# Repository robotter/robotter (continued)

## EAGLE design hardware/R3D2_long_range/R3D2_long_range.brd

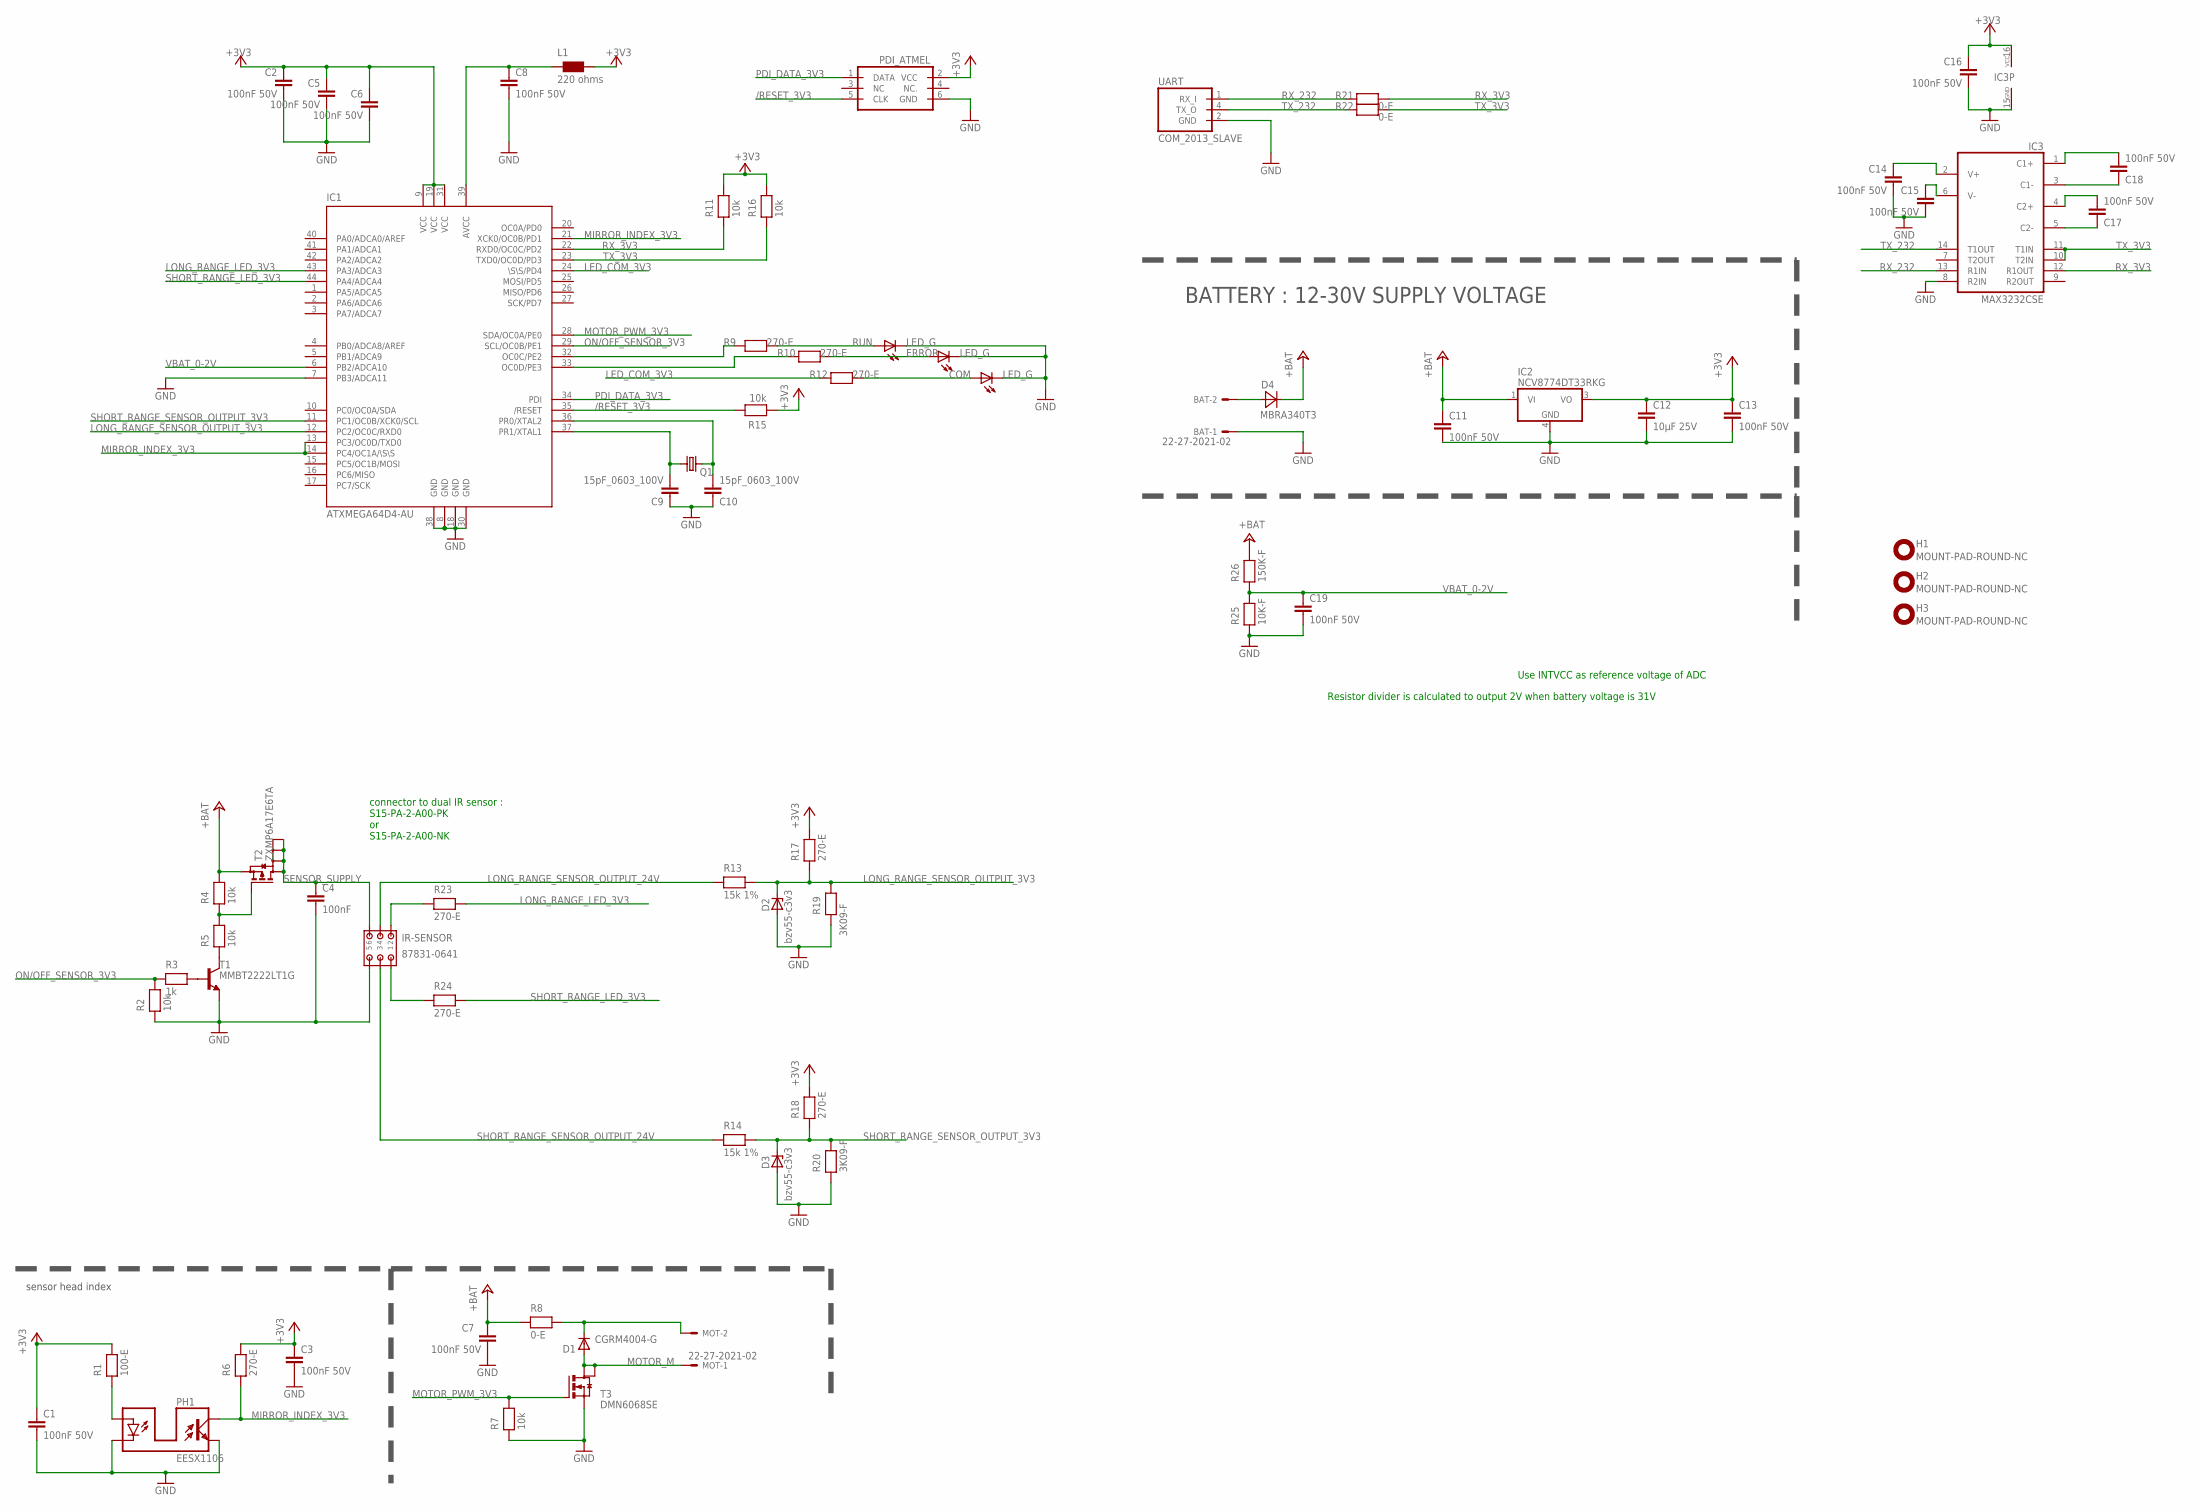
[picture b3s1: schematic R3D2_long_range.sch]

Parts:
BAT: 22-27-2021-02; 6410-02
C1, C2, C3, C5, C6, C7, C8, C13, C14, C15, C16, C17, C18: 100nF 50V; C0603
C4: 100nF; C0603
C9, C10: 15pF_0603_100V; C0603
C11, C19: 100nF 50V; C0805
C12: 10µF 25V; C1210
COM: LED_G; CHIP-LED0805
D1: CGRM4004-G; SOD-123_MINI-SMA
D2, D3: bzv55-c3v3; SOD80C
D4: MBRA340T3; SMA
ERROR: LED_G; CHIP-LED0805
H1, H2, H3: MOUNT-PAD-ROUND-NC; 3,0-PAD_NC
IC1: ATXMEGA64D4-AU; TQFP44
IC2: NCV8774DT33RKG; DPACK_3
IC3: MAX3232CSE; SO16
IR-SENSOR: 87831-0641
L1: 220 ohms; R0603
MOT: 22-27-2021-02; 6410-02
PDI_ATMEL: PDI_ATMELL; ML6L
PH1: EESX1106
Q1: CRYSTAL_16MHZ_5032; CRYSTAL_5032
R1: 100-E; R0805
R2, R4, R5, R7, R11, R15, R16: 10k; R0603
R3: 1k; R0603
R6, R9, R10, R12, R17, R18, R23, R24: 270-E; R0805
R8, R21, R22: 0-E; R0805
R13, R14: 15k 1%; R0603
R19, R20: 3K09-F; R0603
R25: 10K-F; R0603
R26: 150K-F; R0603
RUN: LED_G; CHIP-LED0805
T1: MMBT2222LT1G; SOT23-BEC
T2: ZXMP6A17E6TA; SOT26
T3: DMN6068SE; SOT223
UART: COM_2013_SLAVE; MICROMATCH-4_SMD

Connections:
+3V3: C1.1, C2.1, C3.1, C5.1, C6.1, C12.1, C13.1, C16.1, IC1.9 (VCC), IC1.19 (VCC), IC1.31 (VCC), IC2.3 (VO), IC3.16 (VCC), L1.2, PDI_ATMEL.2 (VCC), R1.2, R6.2, R11.2, R15.1, R16.2, R17.2, R18.2
+24V: C7.1, C11.1, D4.C, IC2.1 (VI), R4.2, R8.1, R26.2, T2.4 (S)
/RESET_3V3: IC1.35 (/RESET), PDI_ATMEL.5 (CLK), R15.2
GND: BAT.1, C1.2, C2.2, C3.2, C4.2, C5.2, C6.2, C7.2, C8.2, C9.1, C10.1, C11.2, C12.2, C13.2, C14.2, C15.2, C16.2, C19.2, COM.C, D2.A, D3.A, ERROR.C, IC1.7 (PB3/ADCA11), IC1.8 (GND), IC1.18 (GND), IC1.30 (GND), IC1.38 (GND), IC2.4 (GND), IC3.8 (R2IN), IC3.15 (GND), IR-SENSOR.5, PDI_ATMEL.6 (GND), PH1.E (TRANSISTOR_E), PH1.K (LED_C), R2.1, R7.1, R19.1, R20.1, R25.1, RUN.C, T1.E, T3.3 (S), UART.2 (GND)
LED_COM_3V3: IC1.24 (\S\S/PD4), R12.1
LONG_RANGE_LED_3V3: IC1.43 (PA3/ADCA3), R23.2
LONG_RANGE_SENSOR_OUTPUT_3V3: D2.C, IC1.12 (PC2/OC0C/RXD0), R13.2, R17.1, R19.2
LONG_RANGE_SENSOR_OUTPUT_24V: IR-SENSOR.4, R13.1
MIRROR_INDEX_3V3: IC1.13 (PC3/OC0D/TXD0), IC1.14 (PC4/OC1A/\S\S), IC1.21 (XCK0/OC0B/PD1), PH1.C (TRANSISTOR_C), R6.1
MOTOR_M: D1.A, MOT.1, T3.2 (D), T3.4 (D)
MOTOR_PWM_3V3: IC1.28 (SDA/OC0A/PE0), R7.2, T3.1 (G)
unnamed: C18.1, IC3.1 (C1+)
unnamed: R9.2, RUN.A
unnamed: D1.C, MOT.2, R8.2
unnamed: ERROR.A, R10.2
unnamed: C18.2, IC3.3 (C1-)
unnamed: C17.1, IC3.4 (C2+)
unnamed: COM.A, R12.2
unnamed: BAT.2, D4.A
unnamed: IC1.32 (OC0C/PE2), R9.1
unnamed: IC1.33 (OC0D/PE3), R10.1
unnamed: C14.1, IC3.2 (V+)
unnamed: C15.1, IC3.6 (V-)
unnamed: C10.2, IC1.36 (PR0/XTAL2), Q1.2
unnamed: PH1.A (LED_A), R1.1
unnamed: C8.1, IC1.39 (AVCC), L1.1
unnamed: IR-SENSOR.2, R23.1
unnamed: IR-SENSOR.1, R24.1
unnamed: C17.2, IC3.5 (C2-)
unnamed: C9.2, IC1.37 (PR1/XTAL1), Q1.1
unnamed: R3.2, T1.B
unnamed: R5.1, T1.C
unnamed: R4.1, R5.2, T2.3 (G)
ON/OFF_SENSOR_3V3: IC1.29 (SCL/OC0B/PE1), R2.2, R3.1
PDI_DATA_3V3: IC1.34 (PDI), PDI_ATMEL.1 (DATA)
RX_3V3: IC1.22 (RXD0/OC0C/PD2), IC3.12 (R1OUT), R11.1, R21.2
RX_232: IC3.13 (R1IN), R21.1, UART.1 (RX_I)
SENSOR_SUPPLY: C4.1, IR-SENSOR.6, T2.1 (D), T2.2 (D), T2.5 (D), T2.6 (D)
SHORT_RANGE_LED_3V3: IC1.44 (PA4/ADCA4), R24.2
SHORT_RANGE_SENSOR_OUTPUT_3V3: D3.C, IC1.11 (PC1/OC0B/XCK0/SCL), R14.2, R18.1, R20.2
SHORT_RANGE_SENSOR_OUTPUT_24V: IR-SENSOR.3, R14.1
TX_3V3: IC1.23 (TXD0/OC0D/PD3), IC3.10 (T2IN), IC3.11 (T1IN), R16.1, R22.2
TX_232: IC3.14 (T1OUT), R22.1, UART.4 (TX_O)
VBAT_0-2V: C19.1, IC1.6 (PB2/ADCA10), R25.2, R26.1

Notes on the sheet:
sensor head index
connector to dual IR sensor : S15-PA-2-A00-PK or S15-PA-2-A00-NK
BATTERY : 12-30V SUPPLY VOLTAGE
Use INTVCC as reference voltage of ADC
Resistor divider is calculated to output 2V when battery voltage is 31V

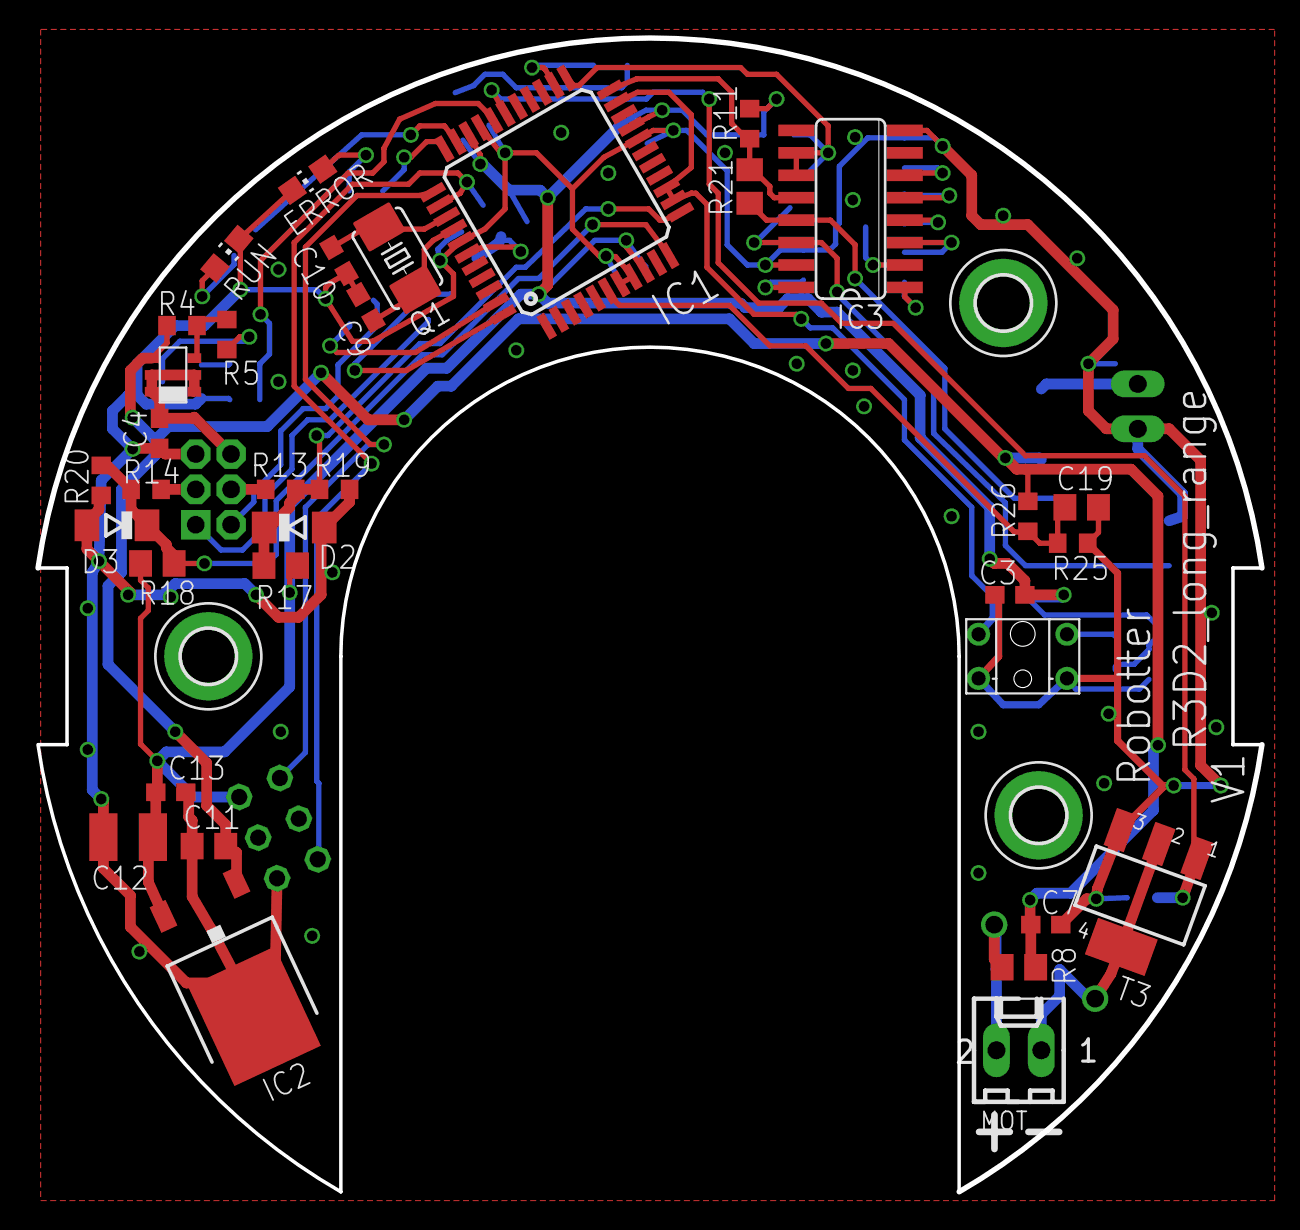
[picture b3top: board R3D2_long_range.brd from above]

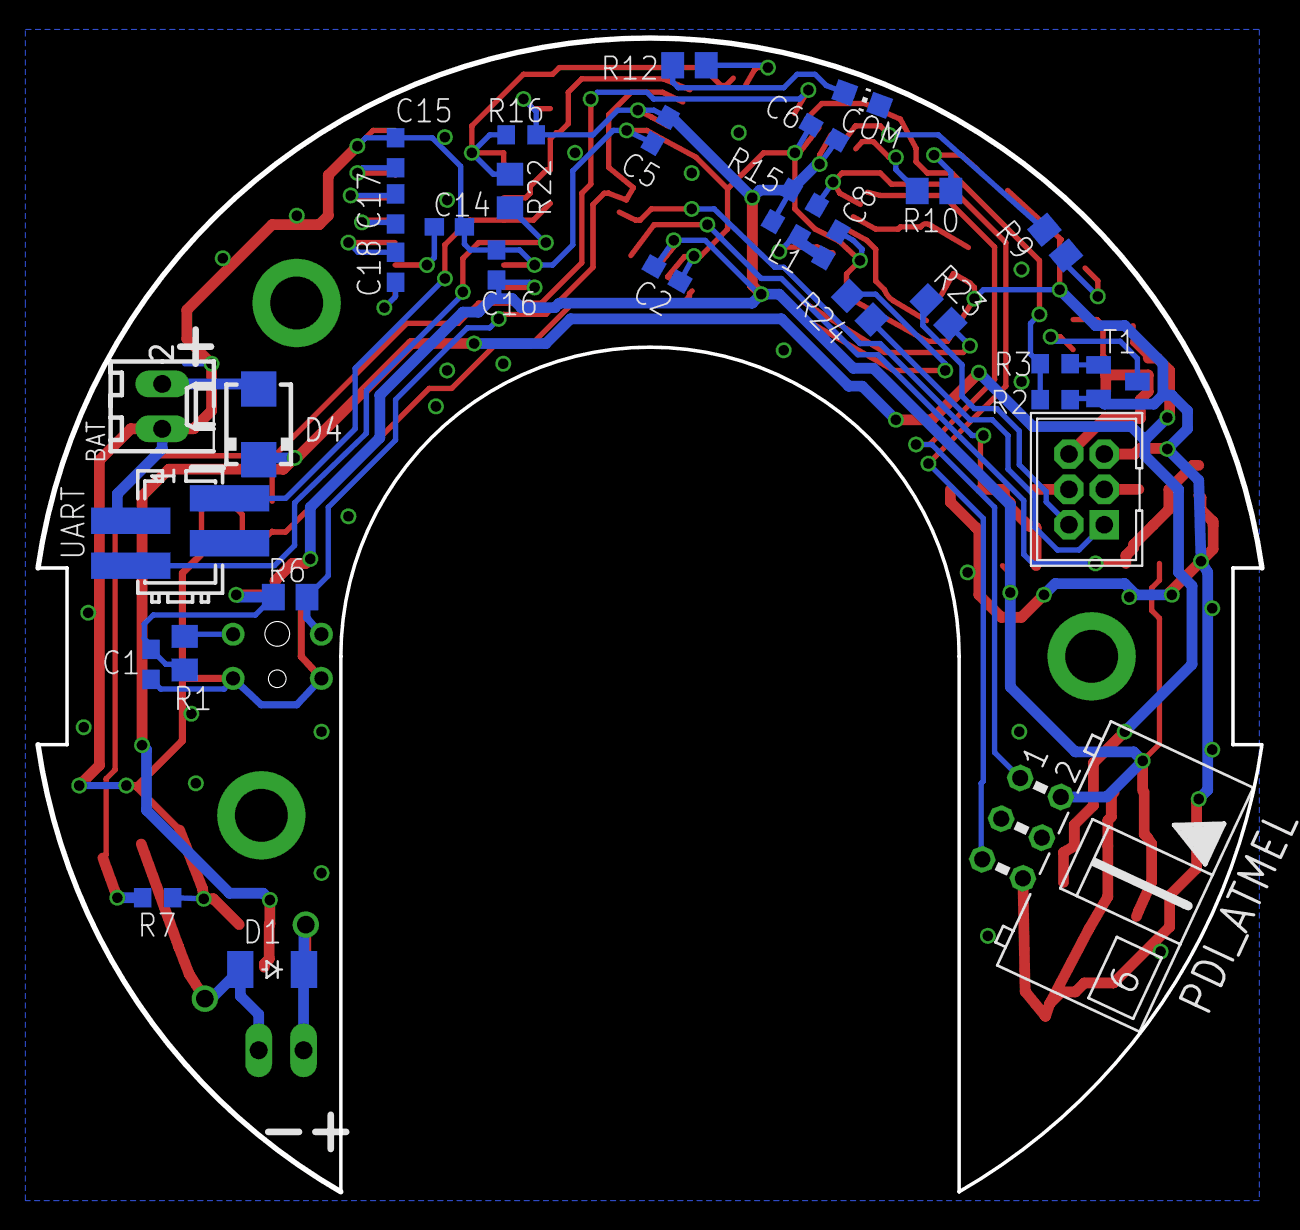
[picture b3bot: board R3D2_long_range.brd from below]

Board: 2 copper layers, 69.3 x 65.3 mm, 69 parts (32 on the bottom side), 44 nets.

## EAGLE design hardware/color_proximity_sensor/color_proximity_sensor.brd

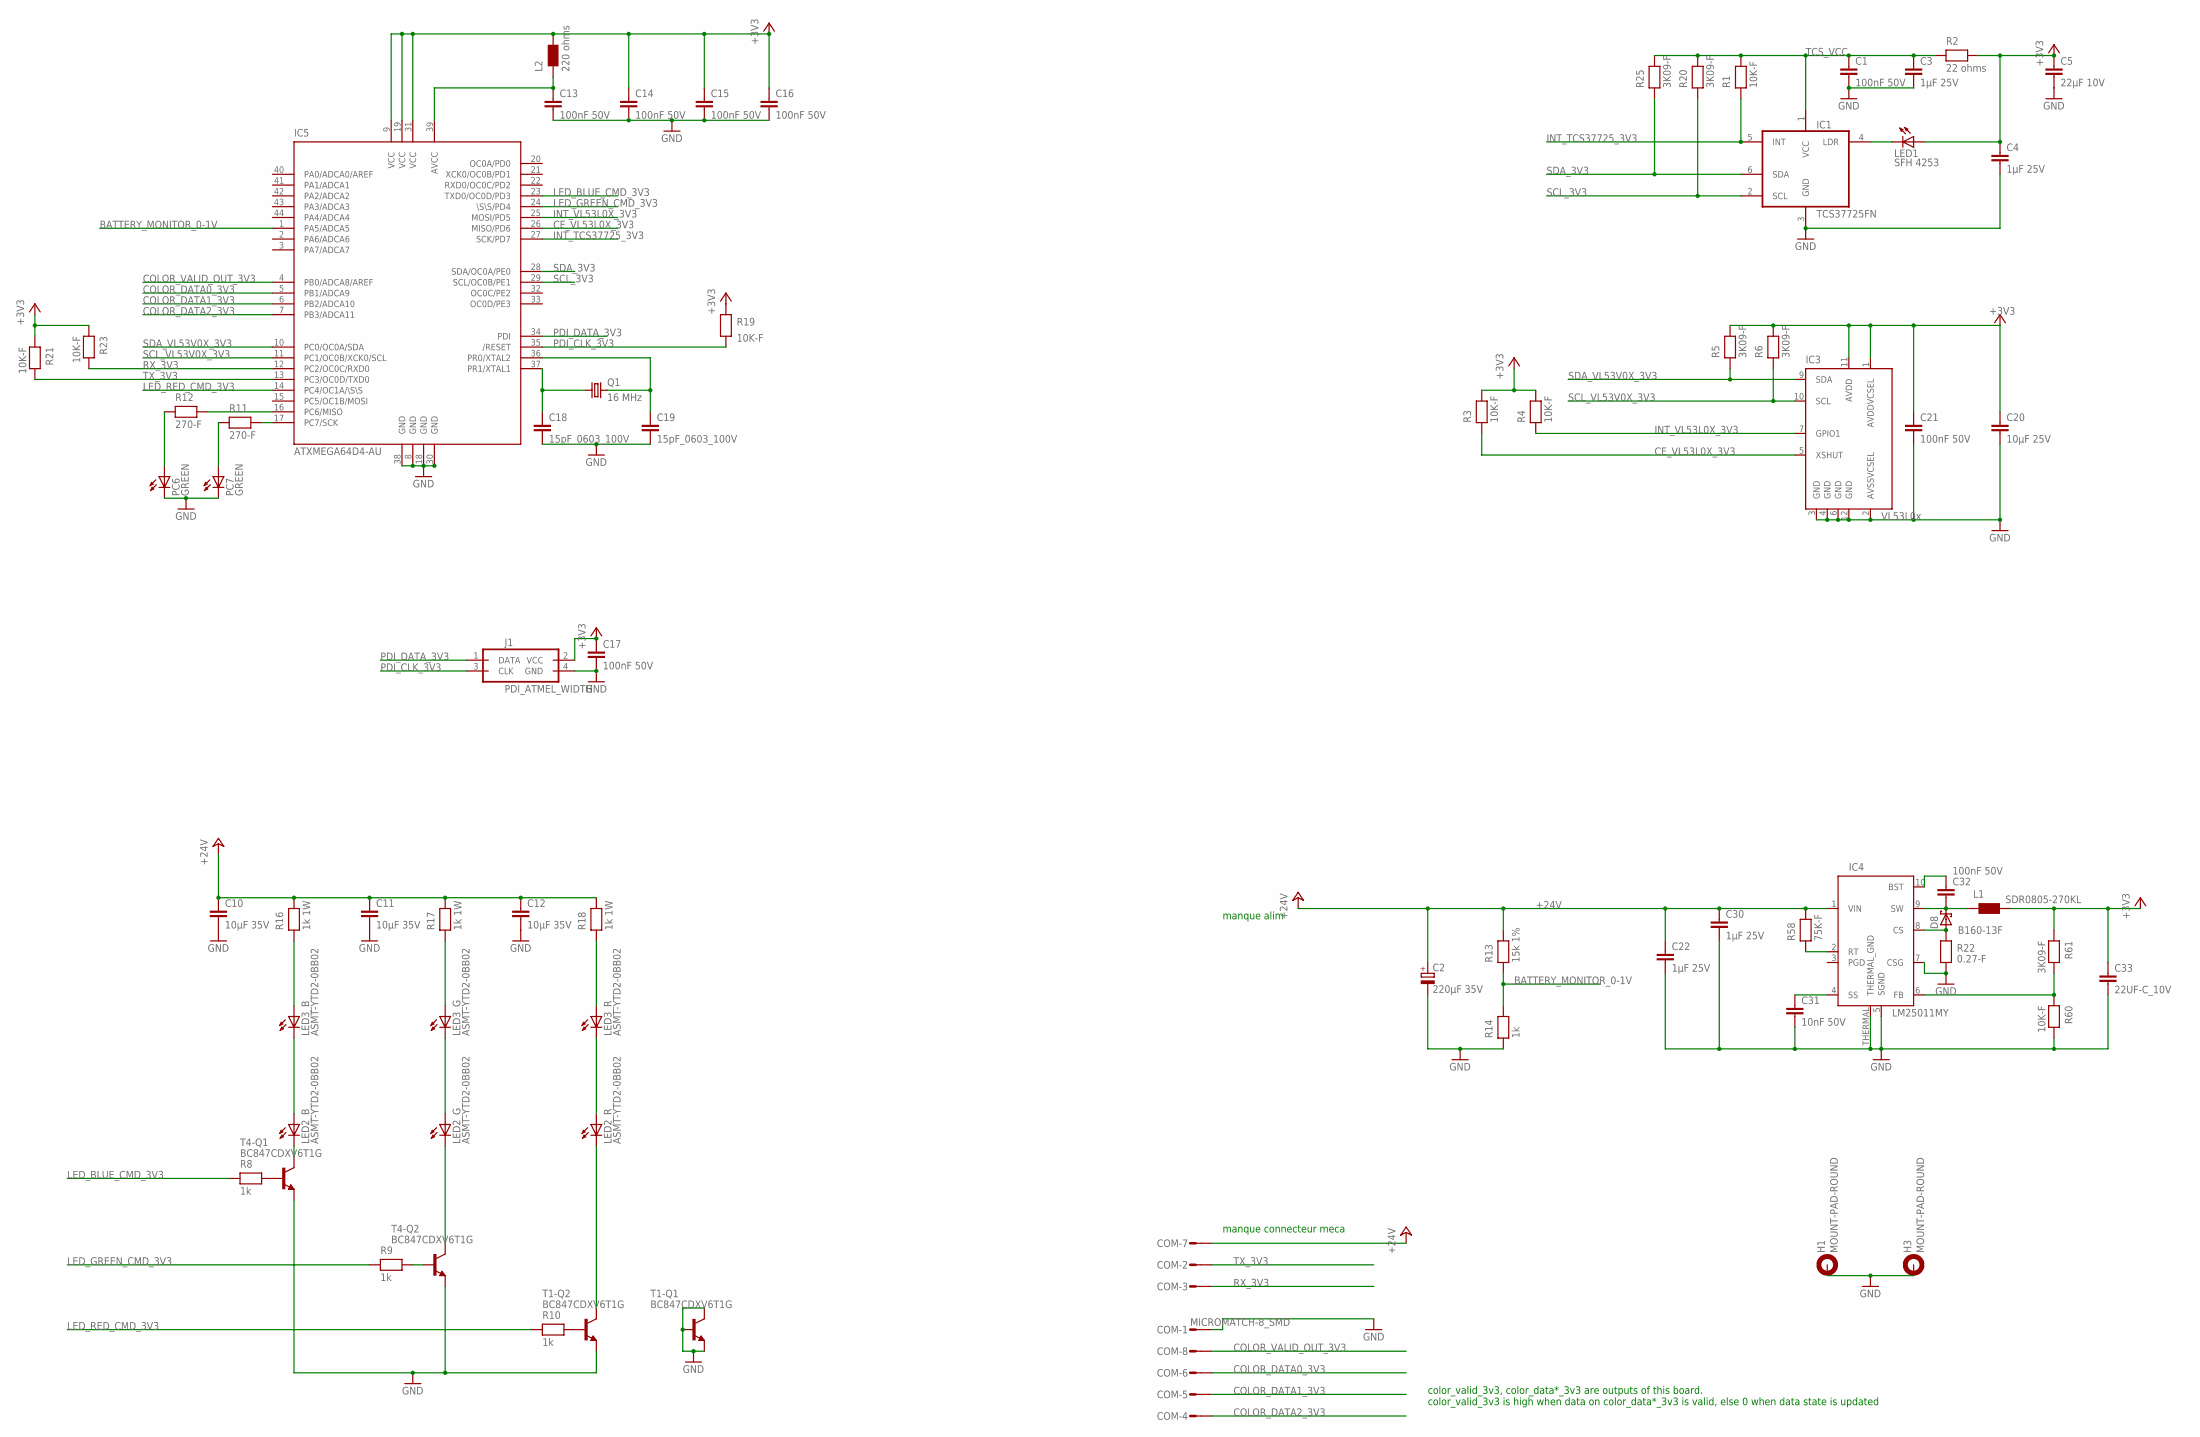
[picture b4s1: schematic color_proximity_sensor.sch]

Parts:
C1, C13, C14, C15, C16, C17, C21, C32: 100nF 50V; C0603
C2: 220µF 35V; PANASONIC_F
C3, C4, C22, C30: 1µF 25V; C1206
C5: 22µF 10V; C1210
C10, C11, C12: 10µF 35V; C1210
C18, C19: 15pF_0603_100V; C0603
C20: 10µF 25V; C1210
C31: 10nF 50V; C0603
C33: 22UF-C_10V; C1210
COM: MICROMATCH-8_SMD
D8: B160-13F; SMA
H1, H3: MOUNT-PAD-ROUND; 2,1-PAD
IC1: TCS37725FN; FN6
IC3: VL53L0x; LGA12
IC4: LM25011MY; MSOP10_THERMAL
IC5: ATXMEGA64D4-AU; TQFP44
J1: PDI_ATMEL_WIDTH; HEADER_2.54MM_2X2W_
L1: SDR0805-270KL; SDR0805
L2: 220 ohms; R0603
LED1: SFH 4253; SFH4253
LED2, LED3: ASMT-YTD2-0BB02; PLCC6
PC6, PC7: GREEN; CHIP-LED0805
Q1: 16 MHz; HC49UP
R1, R3, R4, R19, R21, R23, R60: 10K-F; R0603
R2: 22 ohms; R0603
R5, R6, R20, R25, R61: 3K09-F; R0603
R8, R9, R10: 1k; R0603
R11, R12: 270-F; R0603
R13: 15k 1%; R0805
R14: 1k; R0805
R16, R17, R18: 1k 1W; R2512
R22: 0.27-F; R0603
R58: 75K-F; R0603
T1, T4: BC847CDXV6T1G; SOT563-6

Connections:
+3V3: C4.1, C5.1, C14.1, C15.1, C16.1, C17.1, C20.1, C21.1, C33.1, IC3.1 (AVDDVCSEL), IC3.11 (AVDD), IC5.9 (VCC), IC5.19 (VCC), IC5.31 (VCC), J1.2 (VCC), L1.2, L2.2, LED1.A, R2.2, R3.2, R4.2, R5.2, R6.2, R19.2, R21.1, R23.1, R61.1
+24V: C2.+, C10.1, C11.1, C12.1, C22.1, C30.1, COM.7, IC4.1 (VIN), R13.2, R16.2, R17.2, R18.2, R58.2
BATTERY_MONITOR_0-1V: IC5.1 (PA5/ADCA5), R13.1, R14.2
CE_VL53L0X_3V3: IC3.5 (XSHUT), IC5.26 (MISO/PD6), R3.1
COLOR_DATA0_3V3: COM.6, IC5.5 (PB1/ADCA9)
COLOR_DATA1_3V3: COM.5, IC5.6 (PB2/ADCA10)
COLOR_DATA2_3V3: COM.4, IC5.7 (PB3/ADCA11)
COLOR_VALID_OUT_3V3: COM.8, IC5.4 (PB0/ADCA8/AREF)
GND: C1.2, C2.-, C3.2, C4.2, C5.2, C10.2, C11.2, C12.2, C13.2, C14.2, C15.2, C16.2, C17.2, C18.2, C19.2, C20.2, C21.2, C22.2, C30.2, C31.2, C33.2, COM.1, H1.B2,8, H3.B2,8, IC1.3 (GND), IC3.2 (AVSSVCSEL), IC3.3 (GND), IC3.4 (GND), IC3.6 (GND), IC3.12 (GND), IC4.5 (SGND), IC4.7 (CSG), IC4.THERMAL (THERMAL_GND), IC5.8 (GND), IC5.18 (GND), IC5.30 (GND), IC5.38 (GND), J1.4 (GND), PC6.C, PC7.C, R14.1, R22.1, R60.2, T1.1 (E), T1.3 (C), T1.4 (E), T1.5 (B), T4.1 (E), T4.4 (E)
INT_TCS37725_3V3: IC1.5 (INT), IC5.27 (SCK/PD7), R1.1
INT_VL53L0X_3V3: IC3.7 (GPIO1), IC5.25 (MOSI/PD5), R4.1
LED_BLUE_CMD_3V3: IC5.23 (TXD0/OC0D/PD3), R8.1
LED_GREEN_CMD_3V3: IC5.24 (\S\S/PD4), R9.1
LED_RED_CMD_3V3: IC5.14 (PC4/OC1A/\S\S), R10.1
unnamed: R8.2, T4.5 (B)
unnamed: R9.2, T4.2 (B)
unnamed: IC1.4 (LDR), LED1.C
unnamed: R10.2, T1.2 (B)
unnamed: LED3.4 (A), R18.1
unnamed: LED2.2 (C), T4.6 (C)
unnamed: LED2.3 (C), T1.6 (C)
unnamed: LED2.1 (C), T4.3 (C)
unnamed: LED2.6 (A), LED3.1 (C)
unnamed: LED3.5 (A), R17.1
unnamed: LED3.6 (A), R16.1
unnamed: IC5.17 (PC7/SCK), R11.2
unnamed: LED2.5 (A), LED3.2 (C)
unnamed: LED2.4 (A), LED3.3 (C)
unnamed: IC5.16 (PC6/MISO), R12.2
unnamed: C13.1, IC5.39 (AVCC), L2.1
unnamed: C18.1, IC5.37 (PR1/XTAL1), Q1.1
unnamed: C19.1, IC5.36 (PR0/XTAL2), Q1.2
unnamed: PC7.A, R11.1
unnamed: PC6.A, R12.1
unnamed: C32.2, D8.C, IC4.9 (SW), L1.1
unnamed: D8.A, IC4.8 (CS), R22.2
unnamed: IC4.2 (RT), R58.1
unnamed: C31.1, IC4.4 (SS)
unnamed: IC4.6 (FB), R60.1, R61.2
unnamed: C32.1, IC4.10 (BST)
PDI_CLK_3V3: IC5.35 (/RESET), J1.3 (CLK), R19.1
PDI_DATA_3V3: IC5.34 (PDI), J1.1 (DATA)
RX_3V3: COM.3, IC5.12 (PC2/OC0C/RXD0), R23.2
SCL_3V3: IC1.2 (SCL), IC5.29 (SCL/OC0B/PE1), R20.1
SCL_VL53V0X_3V3: IC3.10 (SCL), IC5.11 (PC1/OC0B/XCK0/SCL), R6.1
SDA_3V3: IC1.6 (SDA), IC5.28 (SDA/OC0A/PE0), R25.1
SDA_VL53V0X_3V3: IC3.9 (SDA), IC5.10 (PC0/OC0A/SDA), R5.1
TCS_VCC: C1.1, C3.1, IC1.1 (VCC), R1.2, R2.1, R20.2, R25.2
TX_3V3: COM.2, IC5.13 (PC3/OC0D/TXD0), R21.2

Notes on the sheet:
manque alim
manque connecteur meca
color_valid_3v3, color_data*_3v3 are outputs of this board. color_valid_3v3 is high when data on color_data*_3v3 is valid, else 0 when data state is updated

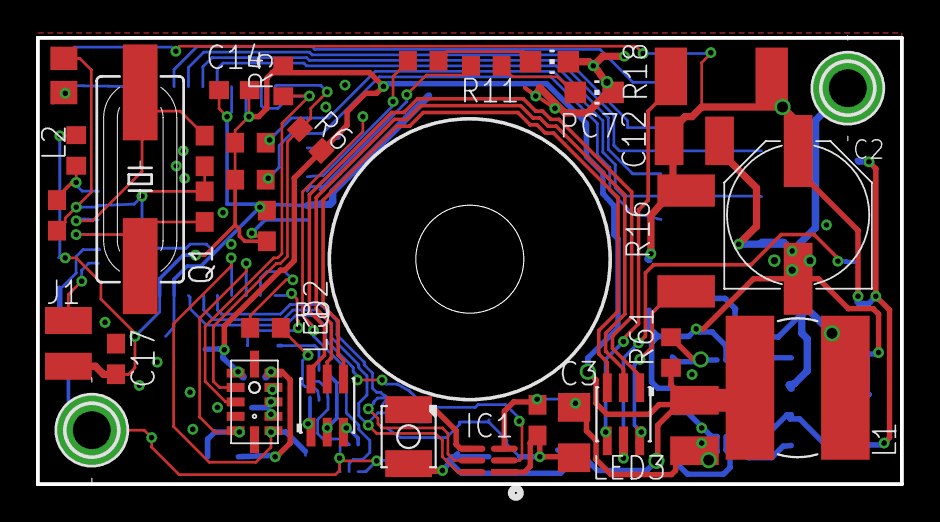
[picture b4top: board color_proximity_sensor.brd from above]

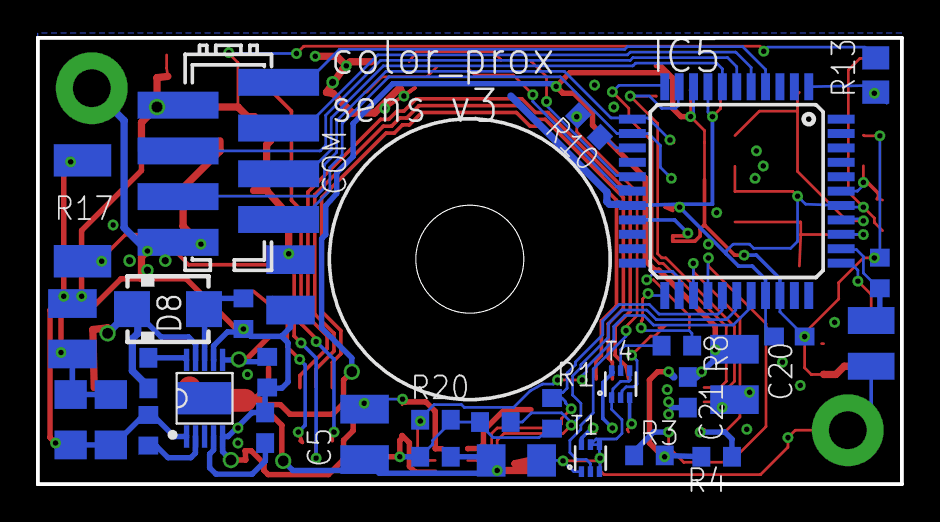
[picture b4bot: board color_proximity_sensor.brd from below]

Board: 2 copper layers, 48.0 x 24.8 mm, 66 parts (31 on the bottom side), 49 nets.
